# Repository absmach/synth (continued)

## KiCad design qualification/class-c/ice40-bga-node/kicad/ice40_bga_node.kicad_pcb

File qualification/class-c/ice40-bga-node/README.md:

# iCE40HX4K BGA node with a USB-C power input (Class C, case 1)

The board carries an iCE40HX4K FPGA in a 121-ball, 0.8 mm-pitch BGA with its supply chain, an SPI boot flash, one 12-pin header and four status LEDs. A USB-C receptacle powers it (power only) and a 6-pin header programs it. It has six copper layers and measures 59.9 x 43.5 mm.

It answers #328 under #40: a board with a BGA part, escaped under the pads, with via and fanout rules, made by an agent driving `synth mcp`. The board carries no firmware and has no USB data path. The figures below are measured on the board file or calculated from datasheets; nothing was built or measured on hardware.

The prompt to reproduce the board is in [`PROMPT.md`](PROMPT.md), written from the finished board. The prompts the agent ran are in the history at `0daaed69`.

## The board

### Parts

| Group                   | Parts                                                                                                                                     |
| ----------------------- | ----------------------------------------------------------------------------------------------------------------------------------------- |
| Power entry             | `J1` Korean Hroparts TYPE-C-31-M-12 USB-C receptacle (5 V from VBUS) with `R_CC1` and `R_CC2`, 5.1 k pull-downs on CC1 and CC2.           |
| Power entry             | `F1` Bourns MF-NSMF050-2 (0.5 A hold, 1 A trip, 13.2 V).                                                                                  |
| Power entry             | `D1` Nexperia PTVS6V0S1UR (6.0 V standoff, 6.67 V minimum breakdown, 10.3 V clamp at 38.8 A), and `C1`.                                   |
| Power entry             | No reverse-polarity stage, since a Type-C receptacle cannot be mated reversed.                                                            |
| CC protection           | `D8` and `D9` TPD1E10B06 bidirectional TVS diodes, one on each CC line at the receptacle, with no rail connection.                        |
| FPGA clock              | `X1`, 25 MHz oscillator on global buffer input `GBIN1` (`iot_197_gbin1`), decoupled by `C41`. The iCE40HX has no internal oscillator.     |
| 3.3 V                   | `U3` AMS1117-3.3 with 4 x 10 uF.                                                                                                          |
| 1.2 V core              | `U4` Texas Instruments TLV70012DDCR, TSOT-23-5, with 1 uF in and 1 uF + 4.7 uF out.                                                       |
| 1.2 V core              | PLL supply `VCCPLL` through the ferrite bead `FB1` (Murata BLM18AG601SN1D) and `C20` to `C22`.                                            |
| FPGA                    | `U1` Lattice iCE40HX4K-BG121 (`VPP_FAST` unconnected), every supply ball decoupled.                                                       |
| Configuration           | `U2` Winbond W25Q128JVSIQ, SOIC-8 208 mil (5.3 mm body), master SPI, with the 6-pin header `J2` for an external programmer.               |
| Configuration           | `CRESET_B` pulled up. `CDONE` drives its LED through N-FET `Q2`, so the open-drain `CDONE` net sees only a gate.                          |
| Programming header `J2` | Pins: `CFG_SS_B` (1, chip select), `CFG_SCK` (2), `CFG_SDI` (3), `CFG_SDO` (4), `CRESET_B` (5), ground (6).                               |
| Programming header `J2` | Names are from the FPGA's side: pin 3 is the flash output (MISO at the programmer) and pin 4 is the flash input (MOSI at the programmer). |
| Programming header `J2` | No 3.3 V pin. A programmer that senses target voltage needs a tap on `TP2`, which is on the 3.3 V rail.                                   |
| Programming procedure   | Hold `CRESET_B` low with an external programmer, write the flash `U2` over SPI, then release `CRESET_B` so the FPGA loads the bitstream.  |
| I/O                     | `J3` JXTCONN JXT-PZ2.54-1X12P-A1, 12 positions (3.3 V, ground and four FPGA I/O through 100 ohm series resistors).                        |
| Indicators              | Four LEDs in one row.                                                                                                                     |
| Test points             | `TP1` to `TP5` on 5 V, 3.3 V, 1.2 V, `CDONE` and `CRESET_B`, all on the bottom side of the board.                                                                              |
| Mounting                | Two M2.5 mounting holes at opposite corners (top left and bottom right), each 4.0 mm from its two board edges.                                                                  |
| FPGA `GNDPLL` | `gndpll0` and `gndpll1` are left unconnected. Lattice DS1040 v3.4, Signal Descriptions: the PLL ground connection is made on the FPGA, so `GNDPLL` must not be connected to the board ground. The PLL is not used. |

### Layout

| Item                    | Value                                                                                                                                                        |
| ----------------------- | ------------------------------------------------------------------------------------------------------------------------------------------------------------ |
| Outline                 | 59.9 x 45.7 mm                                                                                                                                               |
| Copper layers           | 6                                                                                                                                                            |
| Stackup                 | `manufacturer "jlc-advanced"` (the JLCPCB tier with the 0.2 mm drill and via-in-pad on six layers) and `requires via_in_pad`.                                |
| Parts in the BOM        | 63 lines: 56 parts with manufacturer, MPN, rating, datasheet and order number, and 7 board features with no part identity (2 mounting holes, 5 test points). |
| Parts placed in the CPL | 56                                                                                                                                                           |
| Nets                    | 31, all routed                                                                                                                                               |
| Track segments          | 357                                                                                                                                                          |
| Vias                    | 87: 19 at 0.35/0.2 mm, 19 at 0.46/0.2 mm, 49 at 0.6/0.3 mm.                                                                                                  |
| Track length            | 973.2 mm                                                                                                                                                    |
| Zones and planes        | `+3V3` is poured on the inner layers and ground on the outer layers. The 1.2 V core rail and the PLL supply are routed.                                      |
| USB-C placement         | `J1` sits on the left edge with its opening facing out (rotation 270). `escape { off }` is set on `J1`, which is not a ball grid.                            |
| BGA escape              | `escape { method underpad }` on `U1`. The 19 vias at 0.35/0.2 mm are filled and capped vias in the ball pads.                                                |
| Fab package             | `fab/gerbers.zip`, `fab/bom.csv`, `fab/cpl.csv`. `J2` and `J3` are hand-fit through-hole parts.                                                              |
| 3D models               | `models/` holds the STEP body of every part the board references and the board model `ice40_bga_node.step`. The board file reaches them by the relative path `${KIPRJMOD}/../models/`. Mounting holes and fiducials have no body. `J1` uses the HRO TYPE-C-31-M-12 STEP from github.com/ai03-2725/Type-C.pretty (the repository states no licence), placed to match KiCad's footprint. Any other part that KiCad's library has no model for is a simplified box of its envelope. |
| Schematic               | `images/schematic.pdf`: vector pages, one per sheet, plotted by `kicad-cli sch export pdf`. |

### Checks

| Check                              | Result                                             | Notes                                                                                                                                                                                                                                    |
| ---------------------------------- | -------------------------------------------------- | ---------------------------------------------------------------------------------------------------------------------------------------------------------------------------------------------------------------------------------------- |
| KiCad DRC (10.0.8, --refill-zones) | 0 errors, 0 unconnected, 3 warnings                | Warnings: 2 `silk_overlap`, 1 `silk_over_copper` (silkscreen cut back from vias and pads by the exporter, #425).                                                                                                                         |
| KiCad ERC (10.0.8)                 | 0 errors, 0 unconnected, 13 warnings               | Warnings: 8 `lib_symbol_issues`, 5 `lib_symbol_mismatch`.                                                                                                                                                                                |
| DRC rules file                     | Required for a clean DRC                           | `kicad/ice40_bga_node.kicad_dru` lowers the board floors (0.46 mm via diameter, 0.13 mm annular ring) to 0.35 mm and 0.075 mm for vias inside the courtyard of `U1` only.                                                                |
| DRC without the rules file         | `via_diameter` and `annular_width` errors          | Reported on the 19 via-in-pad vias. KiCad loads the rules file when it sits beside the board.                                                                                                                                            |
| Zone fill                          | Refilled                                           | The board is committed with refilled zones, and the Gerbers are plotted from that fill.                                                                                                                                                  |
| Dog-bone escape                    | Does not fit                                       | An export with `escape { method channel }` and without `requires via_in_pad` stopped at the plane stage: `net +3V3: no legal stitching-via position beside the pad at (38.00, 36.40) mm on Top`.                                         |
| Routing engine policy              | `engine_policy_verdict: rejected`                  | Under its strict-size policy, with no rule below the board floor.                                                                                                                                                                        |
| Routing engine via counts          | `claimed_total_vias: 30`, `claimed_via_in_pad: 33` | These count only the vias its own routing and fanout steps placed. Synth's later steps add plane, return and stitch vias and move vias out of pads that do not declare an under-pad escape. The Layout table gives the delivered values. |

### Design figures

| Area          | Item                                      | Value                                                                                                                                        | Basis                                                                     |
| ------------- | ----------------------------------------- | -------------------------------------------------------------------------------------------------------------------------------------------- | ------------------------------------------------------------------------- |
| Configuration | iCE40HX4K bitstream size                  | 135,183 bytes (1,081,464 bits)                                                                                                               | Lattice iCE40 Programming and Configuration, FPGA-TN-02001-3.4, Table 9.2 |
| Configuration | Flash capacity                            | 128 Mbit, holds the bitstream                                                                                                                | Winbond W25Q128JV datasheet                                               |
| Thermal       | `U3` dissipation formula                  | `(5.0 - 3.3) x I`                                                                                                                            | calculated                                                                |
| Thermal       | AMS1117 junction limit                    | 125 degC                                                                                                                                     | AMS1117 datasheet                                                         |
| Thermal       | AMS1117 SOT-223 theta-JA                  | 46 to more than 90 degC/W, depending on copper area; the budget uses 90 degC/W                                                               | AMS1117 datasheet                                                         |
| Power         | `+3V3` load: `U4` TLV70012                | 200 mA (rated output; a linear regulator draws it from the input)                                                                            | TI TLV700 datasheet SBVS173, recommended operating conditions             |
| Power         | `+3V3` load: `U2` W25Q128JV               | 25 mA (`ICC5` and `ICC7` maximum, program and erase)                                                                                         | Winbond W25Q128JV datasheet, DC electrical characteristics                |
| Power         | `+3V3` load: four LEDs with 1 k resistors | 1.3 mA                                                                                                                                       | calculated in the source                                                  |
| Power         | `+3V3` total load                         | 226 mA. The loads are datasheet maxima added together; no operating state reaches all of them at once.                                       | calculated                                                                |
| Thermal       | `U3` at 226 mA                            | 0.38 W, a 35 degC rise: Tj 60 degC at 25 degC ambient, 105 degC at 70 degC ambient                                                           | calculated                                                                |
| Thermal       | Headroom for `J3`                         | About 0.43 A more at 25 degC ambient, or 0.13 A at 70 degC, before Tj reaches 125 degC                                                       | calculated                                                                |
| Thermal       | `F1` bound                                | 0.5 A hold bounds `U3` dissipation at 0.85 W (Tj 101 degC at 25 degC ambient)                                                                | calculated                                                                |
| Thermal       | Warning `W-SYNTH-THERMAL-001`             | Comes from the registry part's 1200 mW package rating at 90 degC/W, not from this board's load                                               | Synth registry part                                                       |
| Protection    | `VBUS`                                    | `D1` (6.0 V standoff) protects `VBUS`.                                                                                                       | Nexperia PTVS6V0S1UR datasheet                                            |
| Protection    | CC lines                                  | `D8` and `D9` (5.5 V standoff) have no connection to `VBUS`, so a source that drives CC before VBUS cannot back-power the rail through them. | TI TPD1E10B06 datasheet                                                   |
| Protection    | `J3`                                      | Carries FPGA I/O through 100 ohm series resistors and has no protection device.                                                              | measured on the board file                                                |
| Assembly      | Via-in-pad land                           | JLCPCB's via-in-pad guide gives the land as the drill plus 0.15 mm.                                                                          | JLCPCB via-in-pad guide                                                   |

### Sourcing

| Item                      | Status                    | Notes                                                                                                                                       |
| ------------------------- | ------------------------- | ------------------------------------------------------------------------------------------------------------------------------------------- |
| `U2` W25Q128JVSIQ package | Checked                   | Manufacturer listings (LCSC, Arrow, RS, JITX) give an 8-pin SOIC of 208 mil. The footprint is `Package_SO:SOIC-8_5.3x5.3mm_P1.27mm`.        |
| `U4` TLV70012 package     | Checked                   | Listed at LCSC only in the DDC (thin) package, which the footprint `TSOT-23-5` matches. Pinout same as DBV: 1 IN, 2 GND, 3 EN, 4 NC, 5 OUT. |
| `D8`, `D9`                | Ordered as TPD1E10B06DYAR | SOD-523, LCSC C3712135, not the DPY X1SON package.                                                                                          |
| `U1` stock                | Unclear                   | The LCSC page for `U1` does not show clear stock. DigiKey 220-2147-ND is the alternative.                                                   |
| LCSC stock figures        | Not firm                  | Stock figures changed between page reads in 2026-11.                                                                                        |

## Not verified by Synth

| Area                 | What is not verified                                                                       |
| -------------------- | ------------------------------------------------------------------------------------------ |
| USB data             | The board has no USB data path. `J1` is a power-only USB-C input.                          |
| Return paths         | The return-path rule is applied by the export gate, and no per-via check is recorded here. |
| CC attach            | No attach test on a 3 A charger was run with the CC diodes `D8` and `D9` fitted.           |
| ESD level            | The board is a bench programming node. No IEC 61000-4-2 level is claimed.                  |
| Thermal              | The 3.3 V budget is calculated from datasheet figures. No temperature was measured.        |
| DFM                  | No JLCDFM or BOM-matching run is recorded.                                                 |
| Independent sign-off | The independent PCB review required by #40 is still open.                                  |

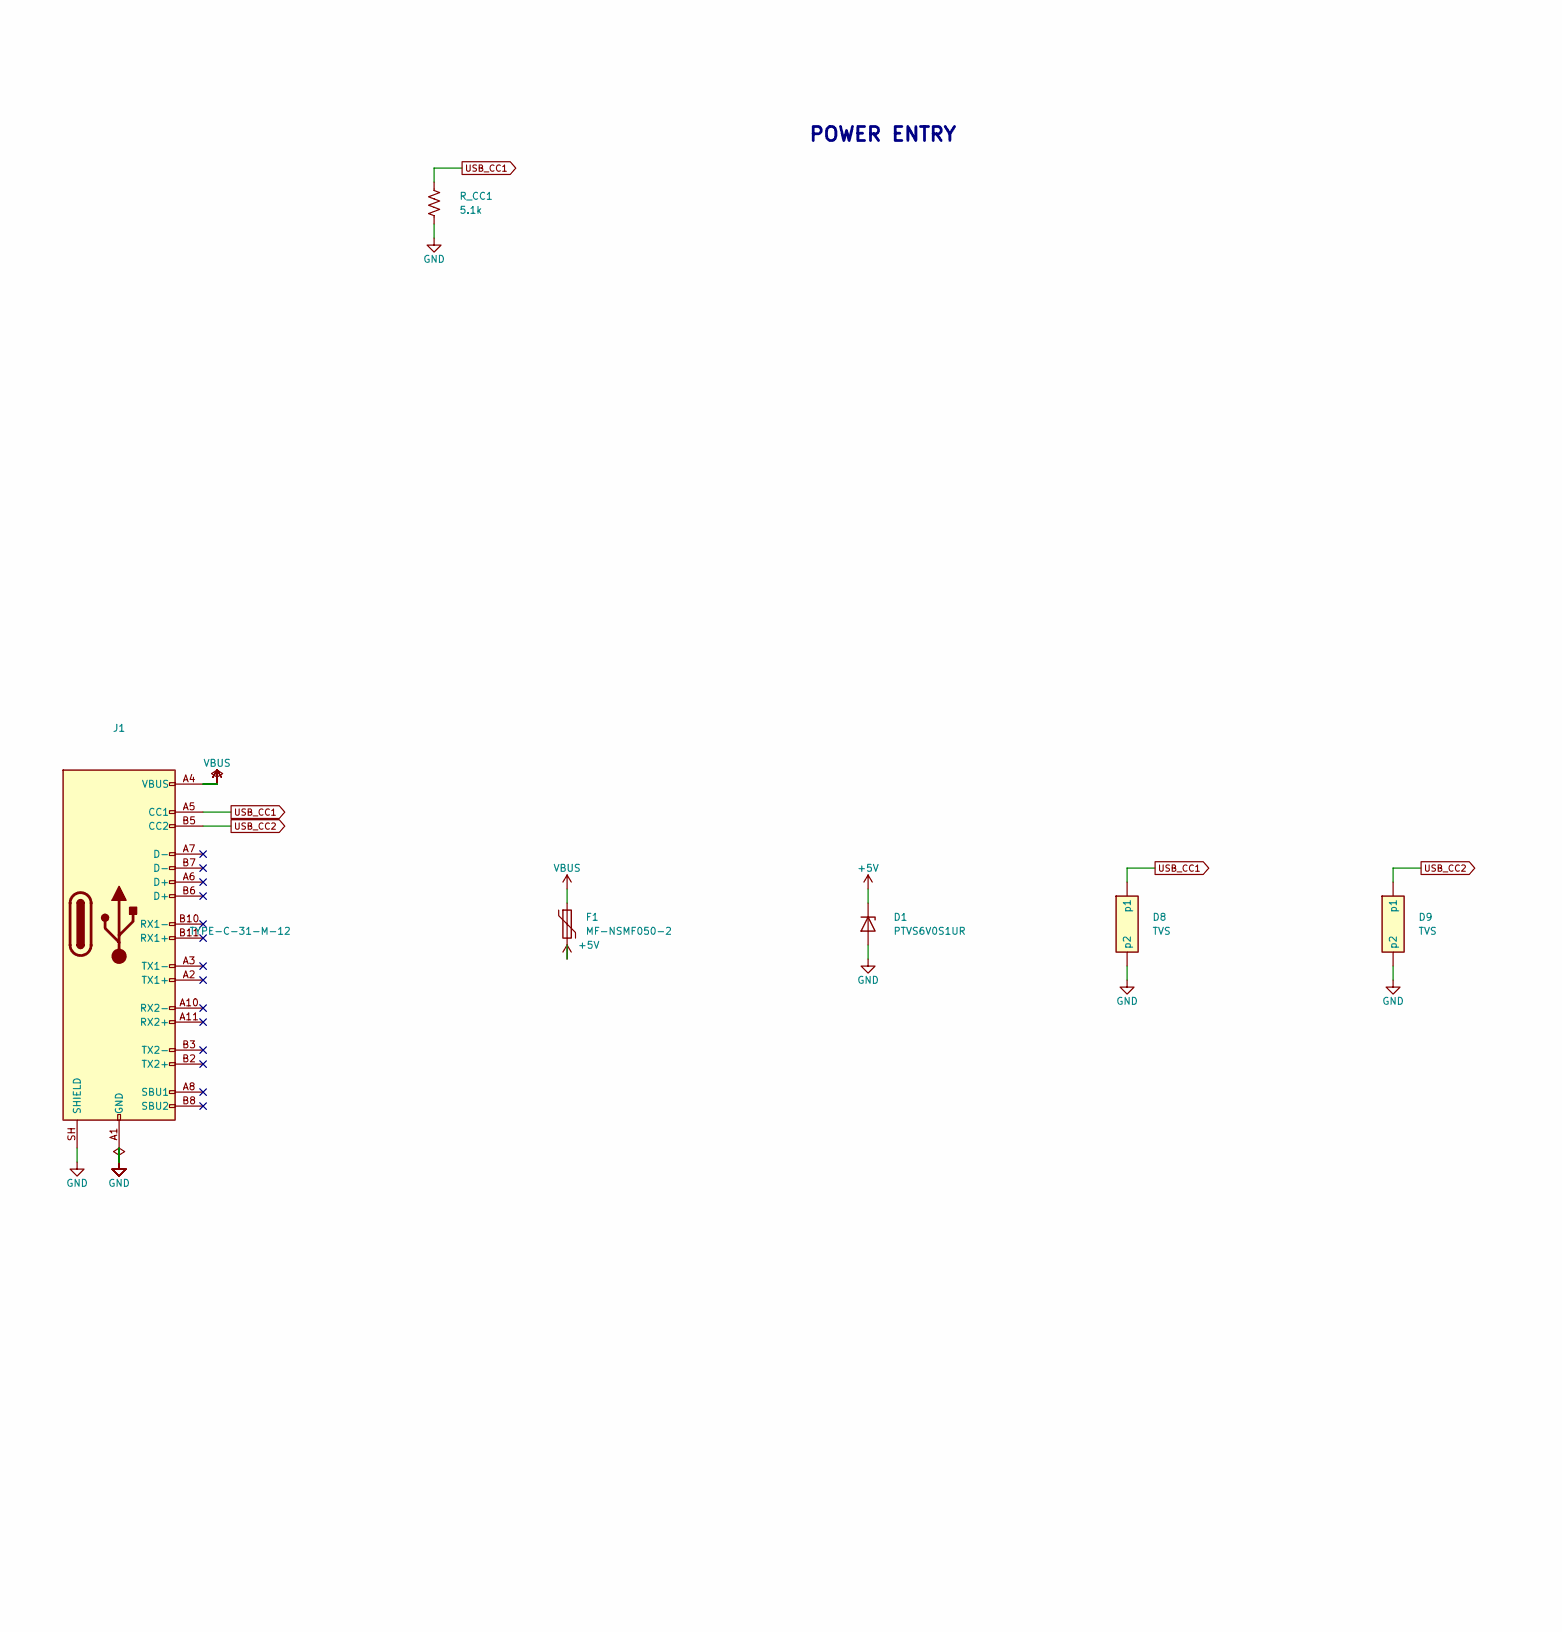
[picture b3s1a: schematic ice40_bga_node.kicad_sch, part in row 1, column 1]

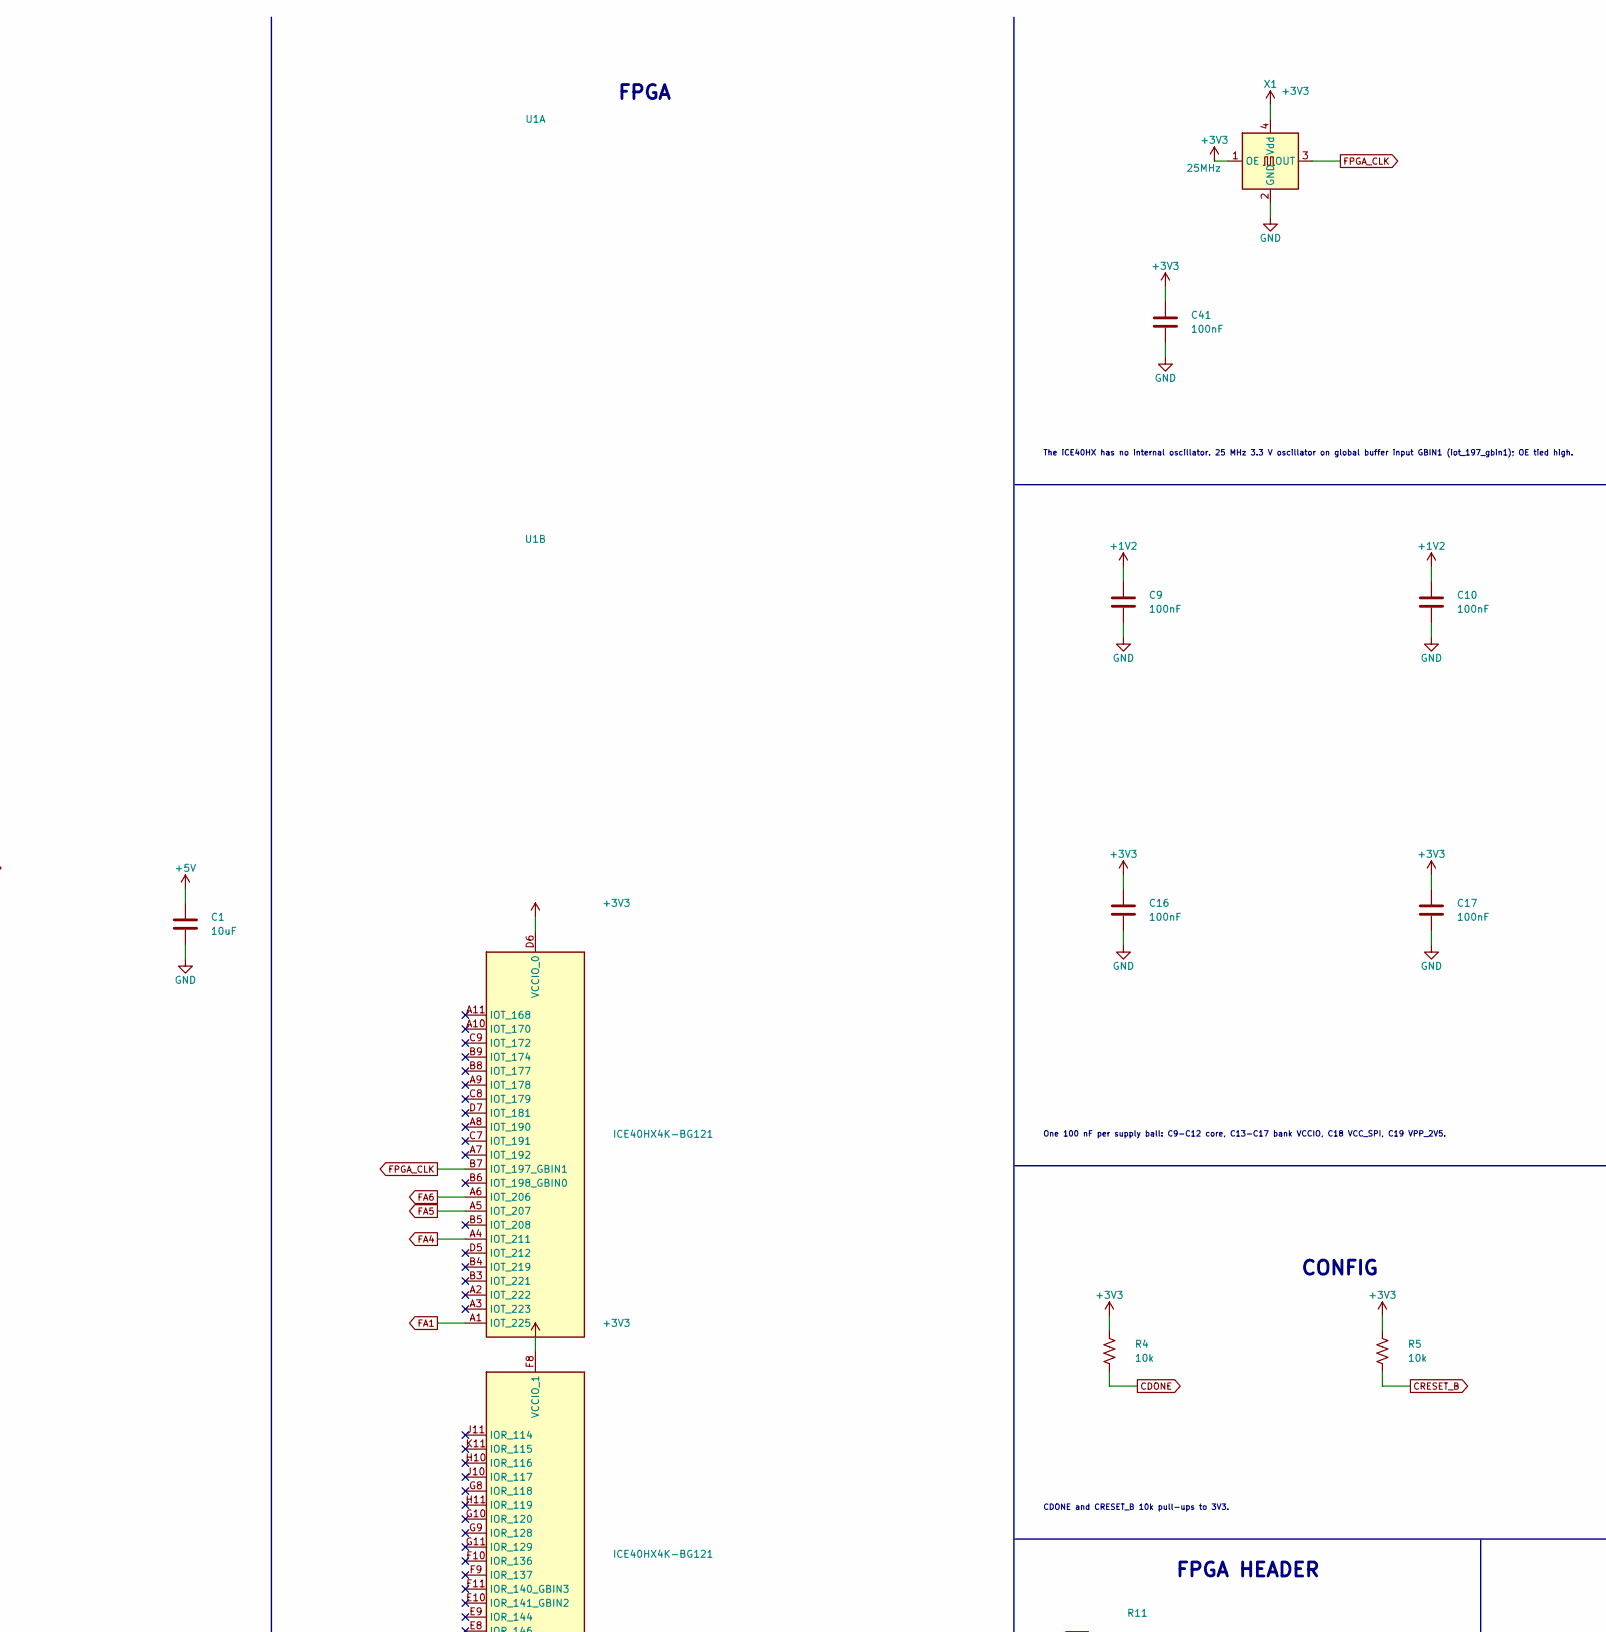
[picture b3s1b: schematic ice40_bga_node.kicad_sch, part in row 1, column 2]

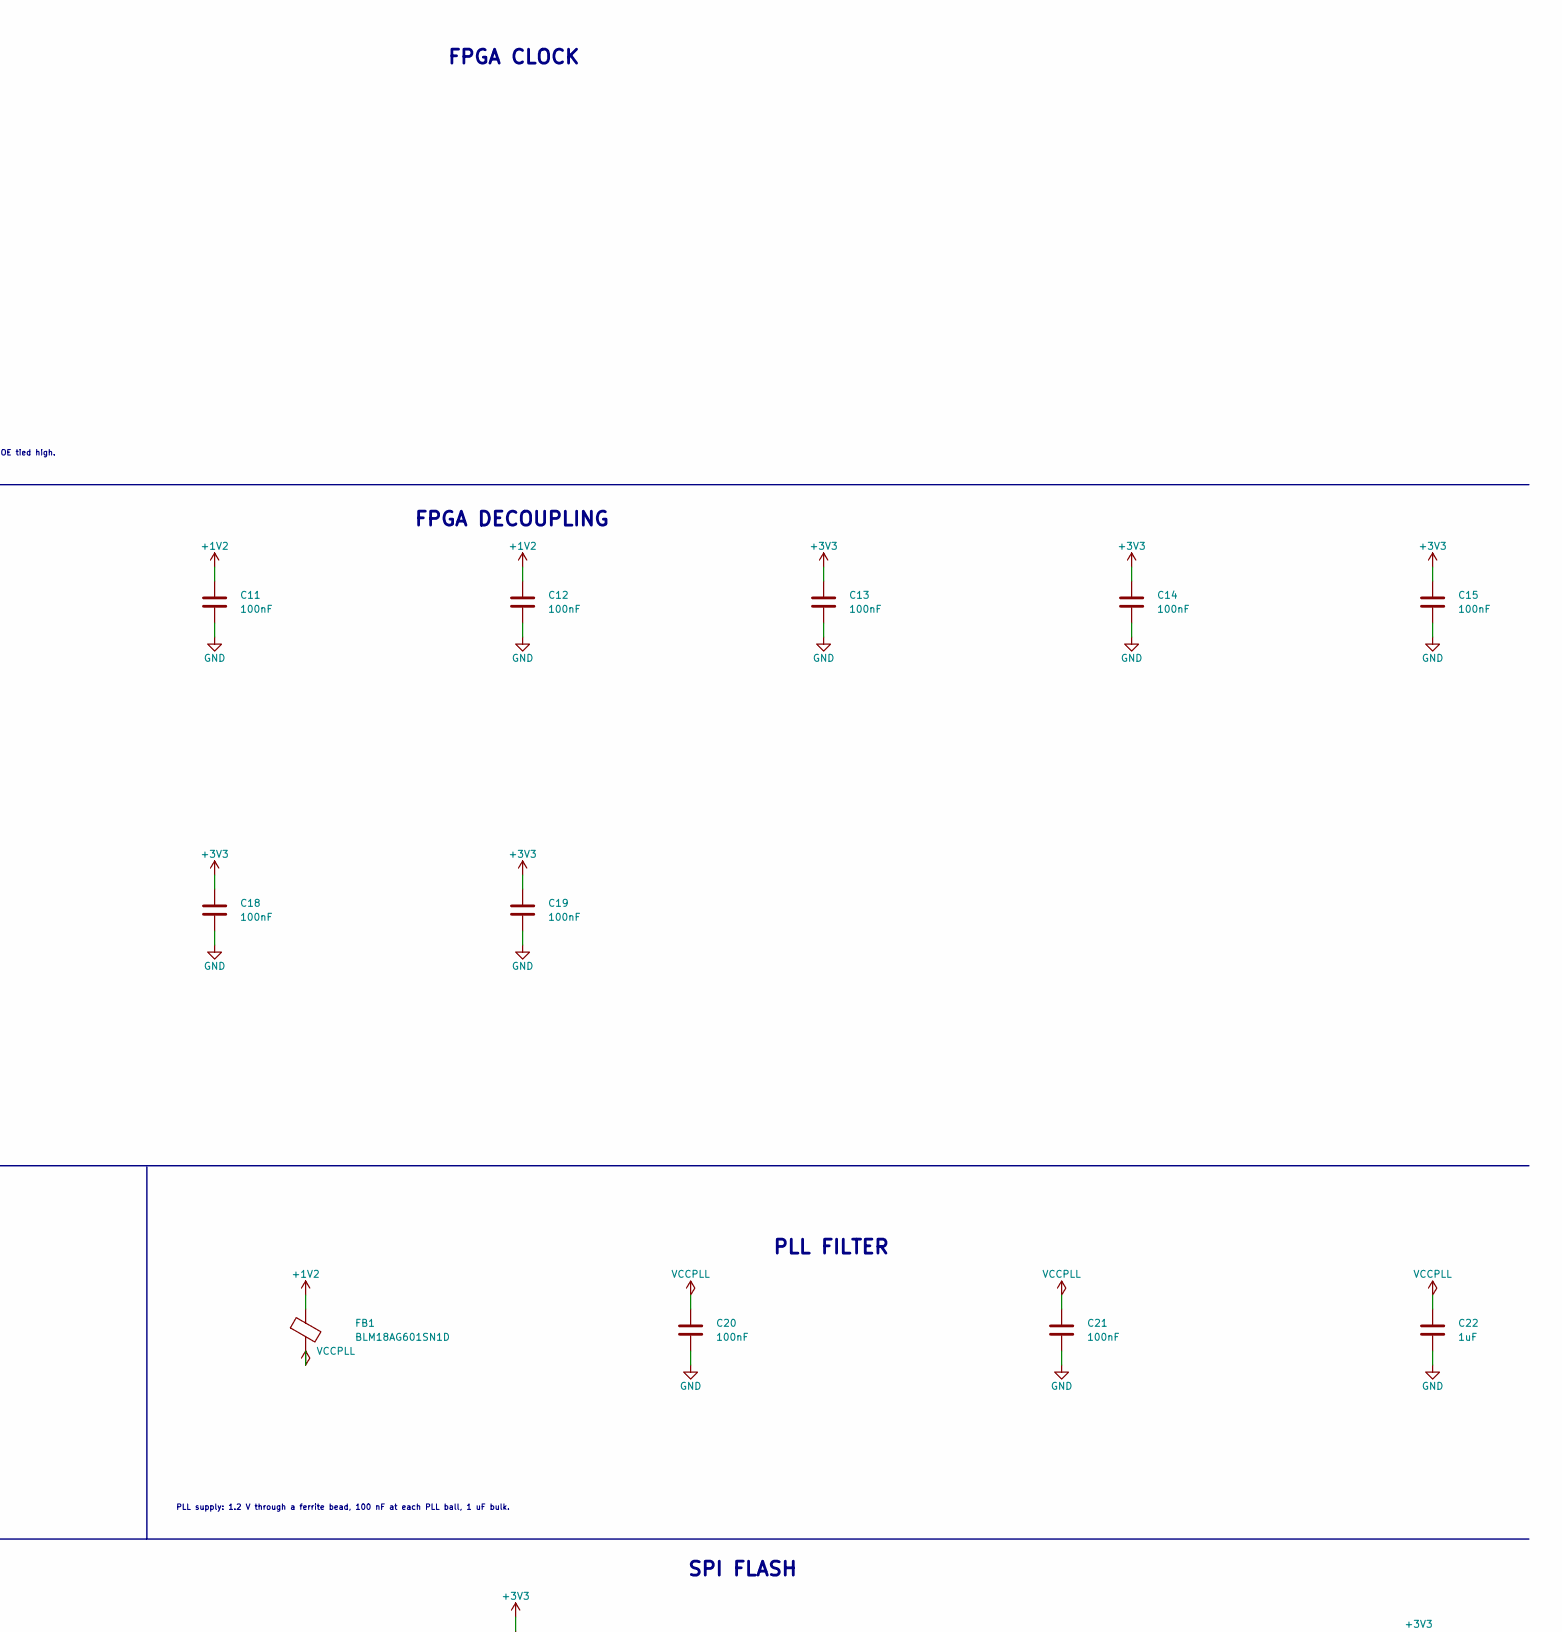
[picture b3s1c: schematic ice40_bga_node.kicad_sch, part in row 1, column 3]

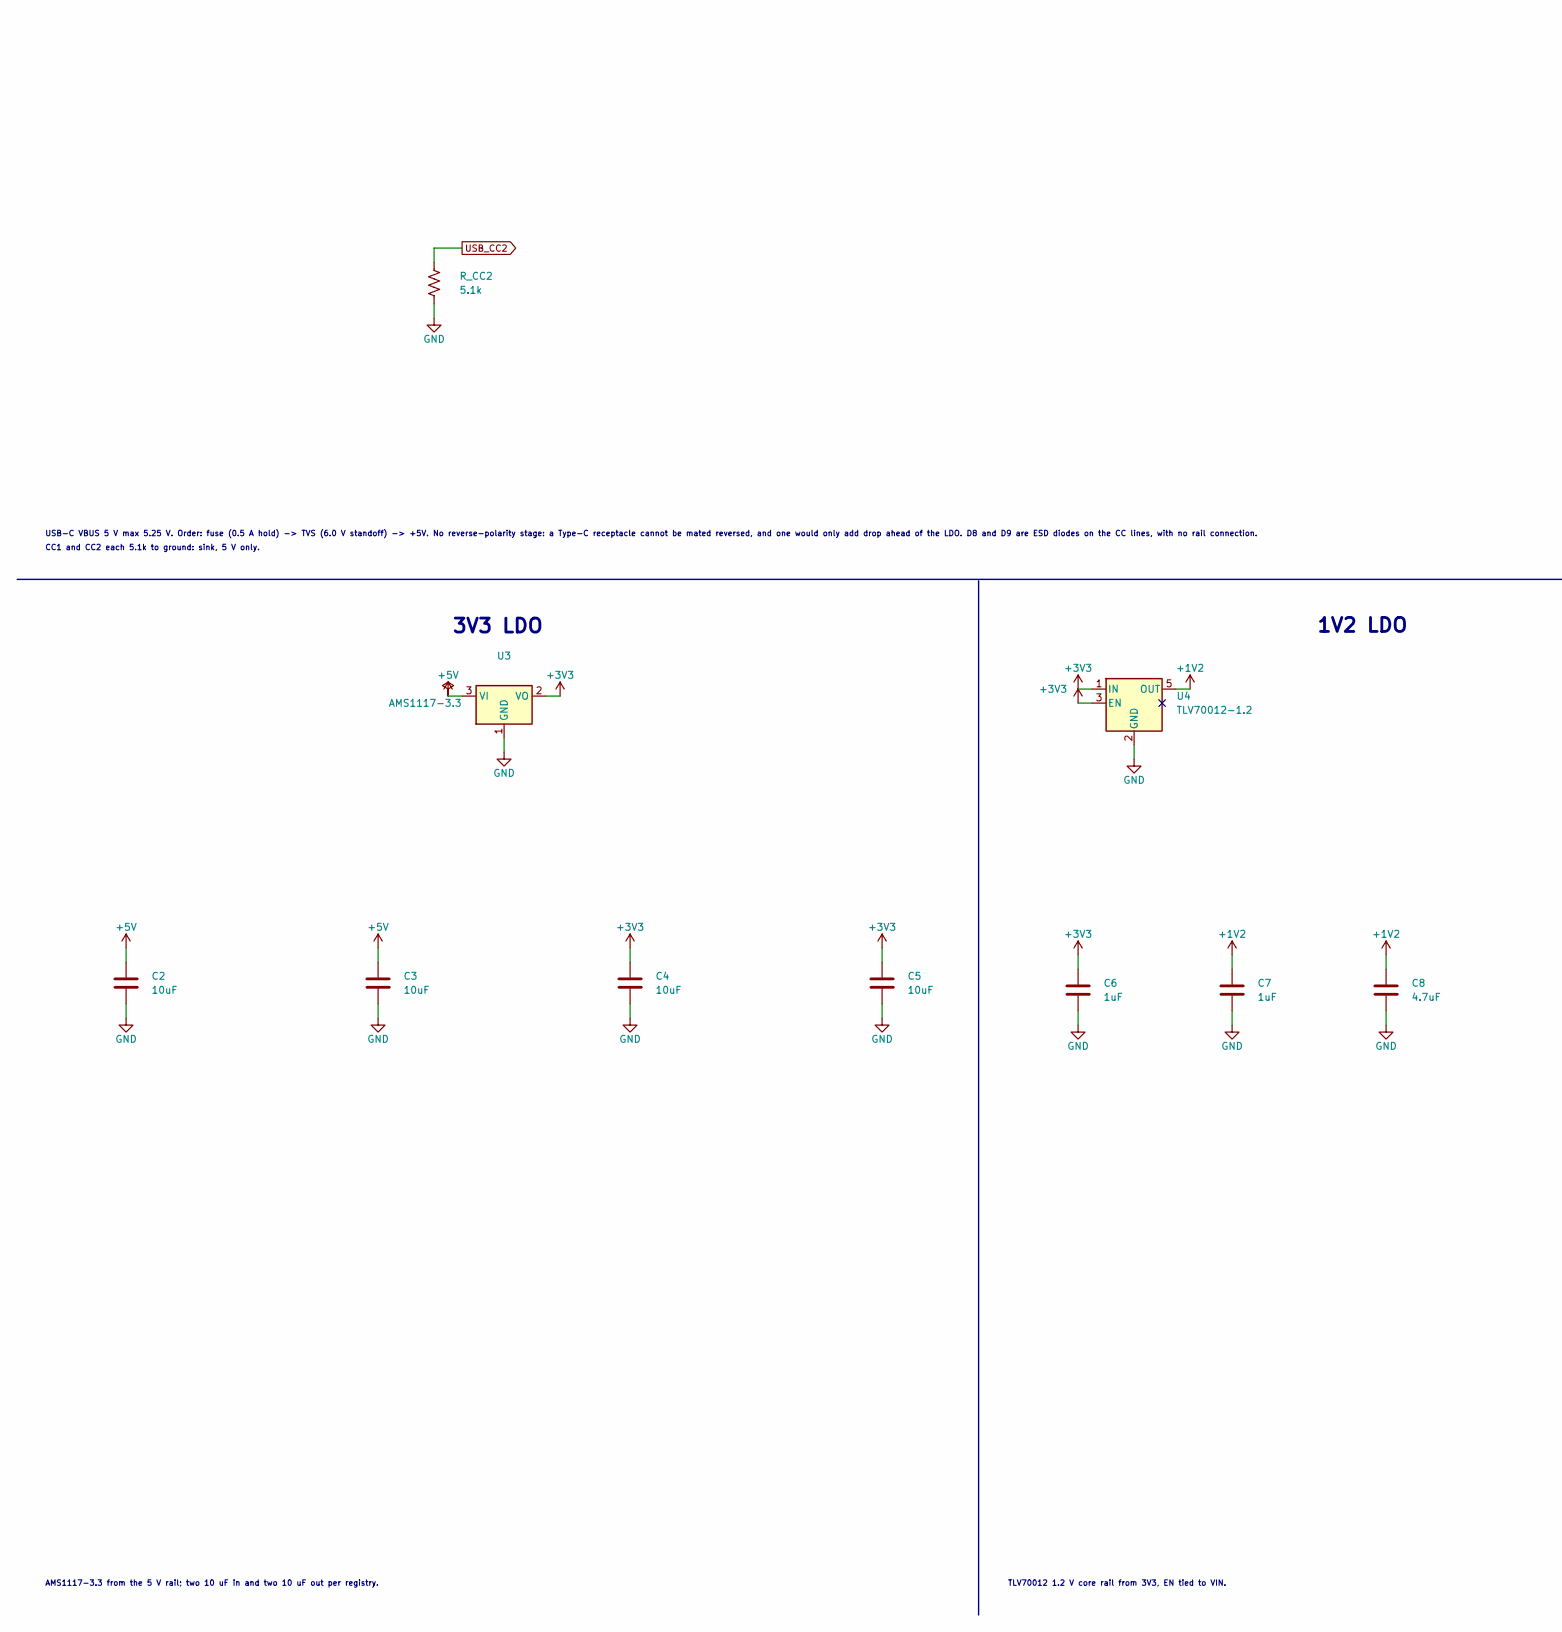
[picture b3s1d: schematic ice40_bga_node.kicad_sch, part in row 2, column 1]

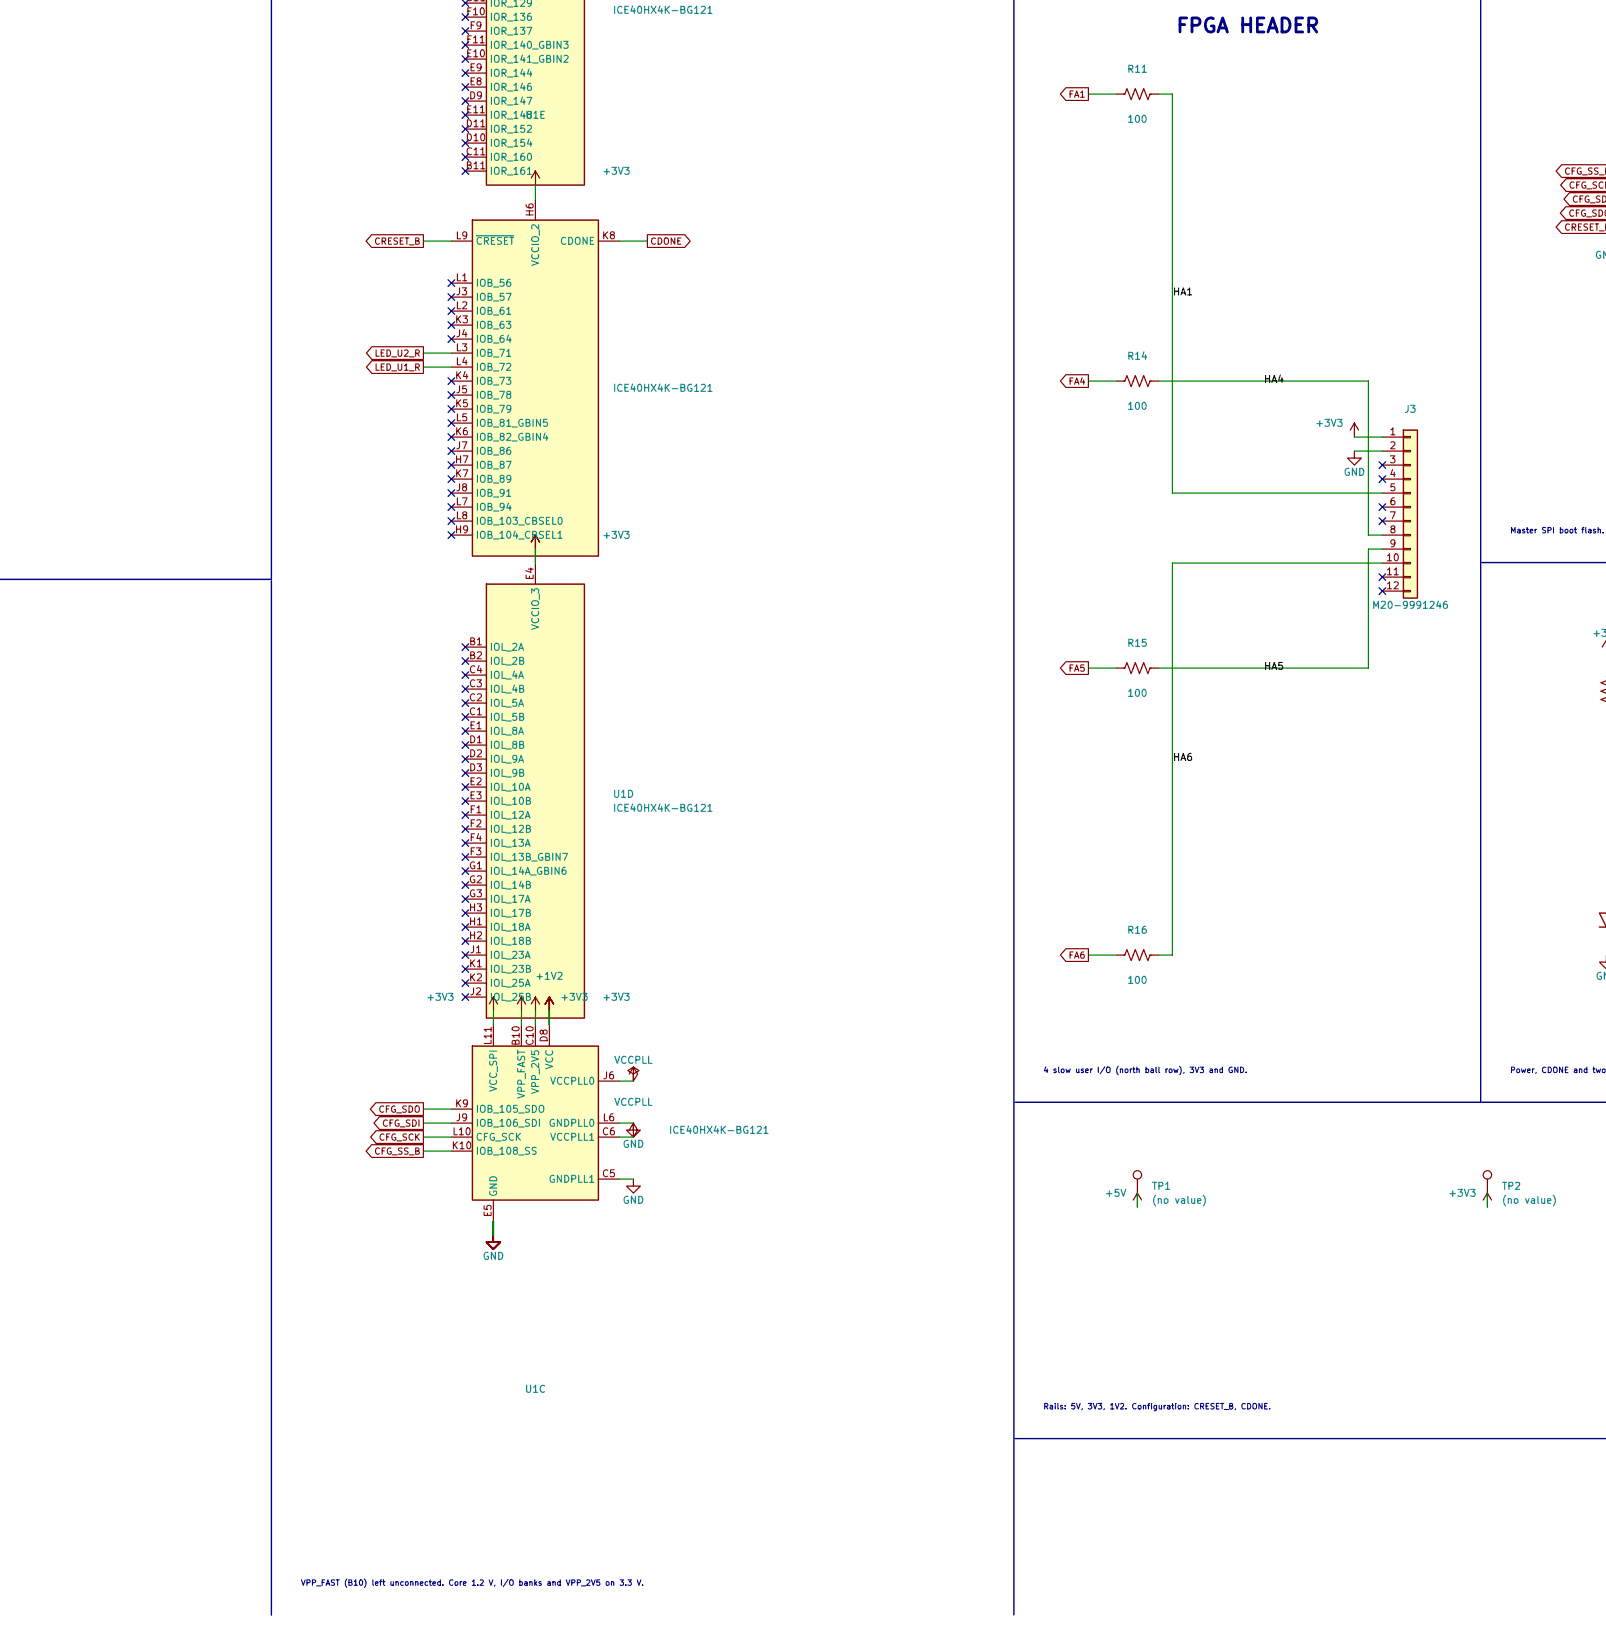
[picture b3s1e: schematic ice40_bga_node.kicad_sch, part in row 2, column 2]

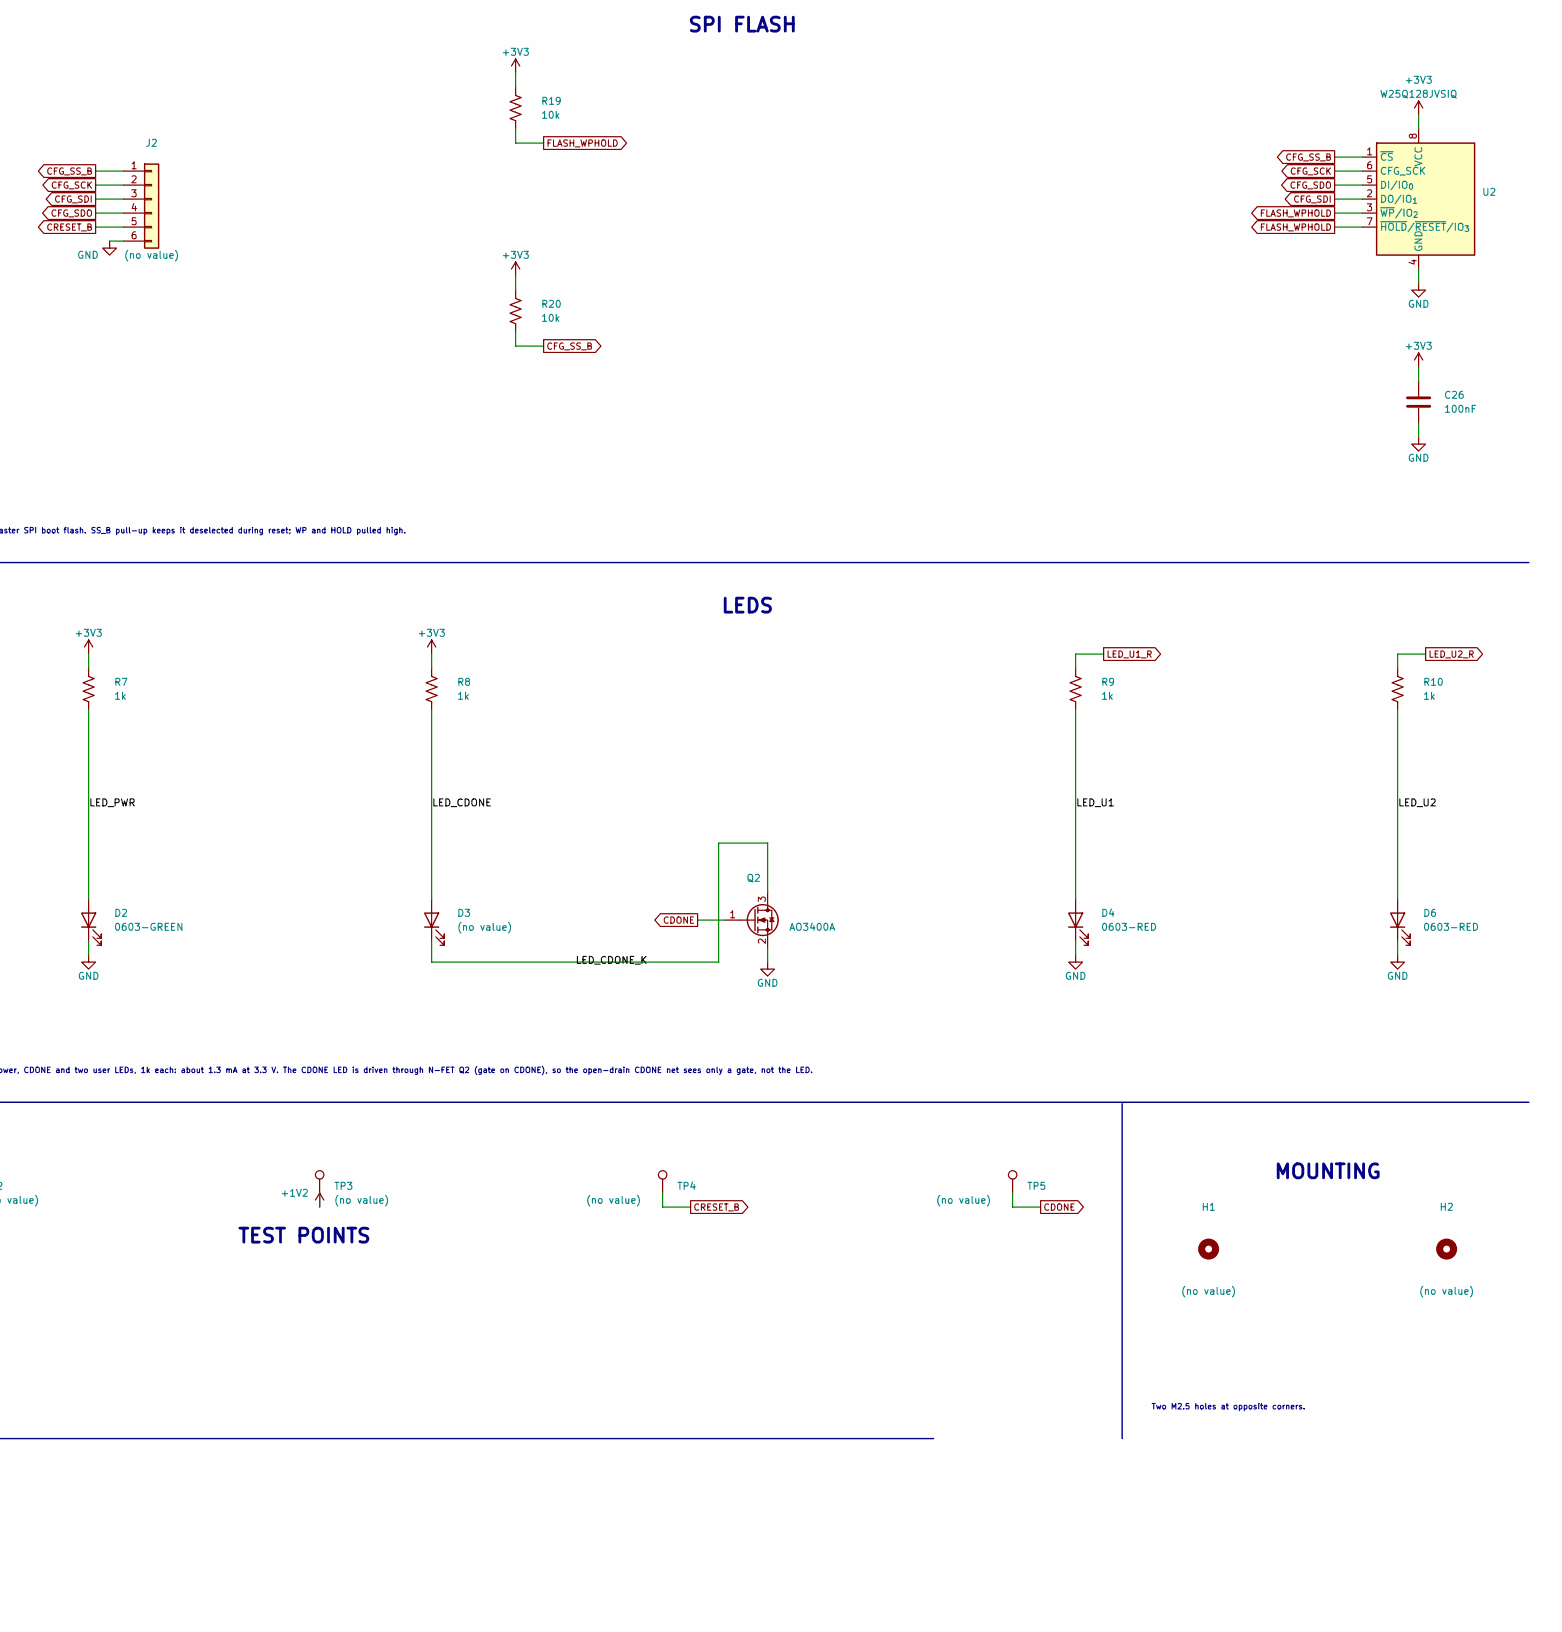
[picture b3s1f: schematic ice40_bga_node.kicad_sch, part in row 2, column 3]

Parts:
C1, C2, C3, C4, C5: 10uF; C_0805_2012Metric
C6, C7, C22: 1uF; C_0603_1608Metric
C8: 4.7uF; C_0805_2012Metric
C9, C10, C11, C12, C13, C14, C15, C16, C17, C18, C19, C20, C21, C26, C41: 100nF; C_0402_1005Metric
D1: PTVS6V0S1UR; Nexperia_CFP3_SOD-123W; MPN PTVS6V0S1UR
D2: 0603-GREEN; LED_0603_1608Metric; MPN 0603-GREEN; LCSC C72043
D3: (no value); LED_0603_1608Metric
D4, D6: 0603-RED; LED_0603_1608Metric; MPN 0603-RED; LCSC C2286
D8, D9: TVS; D_SOD-523; MPN TPD1E10B06DYAR
F1: MF-NSMF050-2; Fuse_1206_3216Metric; MPN MF-NSMF050-2; LCSC C75464
FB1: BLM18AG601SN1D; L_0603_1608Metric; MPN BLM18AG601SN1D; LCSC C19330
H1, H2: (no value); MountingHole_2.5mm
J1: TYPE-C-31-M-12; USB_C_Receptacle_HRO_TYPE-C-31-M-12; MPN TYPE-C-31-M-12; LCSC C165948
J2: (no value); PinHeader_1x06_P2.54mm_Vertical
J3: M20-9991246; PinHeader_1x12_P2.54mm_Vertical; MPN M20-9991246
Q2: AO3400A; SOT-23; MPN AO3400A
R4, R5, R19, R20: 10k; R_0402_1005Metric
R7, R8, R9, R10: 1k; R_0603_1608Metric
R11, R14, R15, R16: 100; R_0402_1005Metric
R_CC1, R_CC2: 5.1k; R_0402_1005Metric
TP1, TP2, TP3, TP4, TP5: (no value); TestPoint_Pad_D1.5mm
U1: ICE40HX4K-BG121; BGA-121_9.0x9.0mm_Layout11x11_P0.8mm_Ball0.4mm_Pad0.35mm_NS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; MPN ICE40HX4K-BG121
U2: W25Q128JVSIQ; SOIC-8_5.3x5.3mm_P1.27mm; MPN W25Q128JVSIQ; LCSC C97521
U3: AMS1117-3.3; SOT-223-3_TabPin2; MPN AMS1117-3.3; LCSC C6186
U4: TLV70012-1.2; TSOT-23-5; MPN TLV70012DDCR; LCSC C69446
X1: 25MHz; Oscillator_SMD_SiT_PQFN-4Pin_5.0x3.2mm

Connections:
+1V2: C7.1, C8.1, C9.1, C10.1, C11.1, C12.1, FB1.1, TP3.1, U1.D4 (VCC), U1.D8 (VCC), U1.H4 (VCC), U1.H8 (VCC), U4.5 (OUT)
+3V3: C4.1, C5.1, C6.1, C13.1, C14.1, C15.1, C16.1, C17.1, C18.1, C19.1, C26.1, C41.1, J3.1, R4.1, R5.2, R7.1, R8.1, R19.1, R20.1, TP2.1, U1.B10 (VPP_FAST), U1.C10 (VPP_2V5), U1.D6 (VCCIO_0), U1.E4 (VCCIO_3), U1.F8 (VCCIO_1), U1.G4 (VCCIO_3), U1.H6 (VCCIO_2), U1.L11 (VCC_SPI), U2.8 (VCC), U3.2 (VO), U4.1 (IN), U4.3 (EN), X1.1 (OE), X1.4 (Vdd)
+5V: C1.1, C2.1, C3.1, D1.1 (K), F1.2, TP1.1, U3.3 (VI)
CDONE: Q2.1 (G), R4.2, TP5.1, U1.K8 (CDONE)
CFG_SCK: J2.2, U1.L10 (IOB_107_SCK), U2.6 (CLK)
CFG_SDI: J2.3, U1.J9 (IOB_106_SDI), U2.2 (DO/IO_{1})
CFG_SDO: J2.4, U1.K9 (IOB_105_SDO), U2.5 (DI/IO_{0})
CFG_SS_B: J2.1, R20.2, U1.K10 (IOB_108_SS), U2.1 (~CS)
CRESET_B: J2.5, R5.1, TP4.1, U1.L9 (~CRESET)
FA1: R11.1, U1.A1 (IOT_225), U1.B1 (IOL_2A)
FA4: R14.1, U1.A4 (IOT_211), U1.A9 (IOT_178), U1.B4 (IOT_219), U1.B9 (IOT_174)
FA5: R15.1, U1.A5 (IOT_207)
FA6: R16.1, U1.A6 (IOT_206), U1.B6 (IOT_198_GBIN0)
FLASH_WPHOLD: R19.2, U2.3 (~WP/IO_{2}), U2.7 (~HOLD/~RESET/IO_{3})
FPGA_CLK: U1.A7 (IOT_192), U1.B7 (IOT_197_GBIN1), X1.3 (OUT)
GND: C1.2, C2.2, C3.2, C4.2, C5.2, C6.2, C7.2, C8.2, C9.2, C10.2, C11.2, C12.2, C13.2, C14.2, C15.2, C16.2, C17.2, C18.2, C19.2, C20.2, C21.2, C22.2, C26.2, C41.2, D1.2 (A), D2.1 (K), D4.1 (K), D6.1 (K), D8.2 (p2), D9.2 (p2), J1.A1 (GND), J1.A12 (GND), J1.B1 (GND), J1.B12 (GND), J1.SH (SHIELD), J2.6, J3.2, Q2.2 (S), R_CC1.2, R_CC2.2, U1.C5 (GNDPLL1), U1.E5 (GND), U1.E6 (GND), U1.E7 (GND), U1.F5 (GND), U1.F6 (GND), U1.F7 (GND), U1.G5 (GND), U1.G6 (GND), U1.G7 (GND), U1.H5 (GND), U1.L6 (GNDPLL0), U2.4 (GND), U3.1 (GND), U4.2 (GND), X1.2 (GND)
HA1: J3.5, R11.2
HA4: J3.8, R14.2
HA5: J3.9, R15.2
HA6: J3.10, R16.2
LED_CDONE: D3.2 (A), R8.2
LED_CDONE_K: D3.1 (K), Q2.3 (D)
LED_PWR: D2.2 (A), R7.2
LED_U1: D4.2 (A), R9.2
LED_U1_R: R9.1, U1.L4 (IOB_72)
LED_U2: D6.2 (A), R10.2
LED_U2_R: R10.1, U1.L3 (IOB_71)
USB_CC1: D8.1 (p1), J1.A5 (CC1), R_CC1.1
USB_CC2: D9.1 (p1), J1.B5 (CC2), R_CC2.1
VBUS: F1.1, J1.A4 (VBUS), J1.A9 (VBUS), J1.B4 (VBUS), J1.B9 (VBUS)
VCCPLL: C20.1, C21.1, C22.1, FB1.2, U1.C6 (VCCPLL1), U1.J6 (VCCPLL0)

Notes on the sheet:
POWER ENTRY
3V3 LDO
1V2 LDO
FPGA
FPGA CLOCK
FPGA DECOUPLING
PLL FILTER
CONFIG
SPI FLASH
LEDS
FPGA HEADER
TEST POINTS
MOUNTING
USB-C VBUS 5 V max 5.25 V. Order: fuse (0.5 A hold) -> TVS (6.0 V standoff) -> +5V. No reverse-polarity stage: a Type-C receptacle cannot be mated reversed, and one would only add drop ahead of the LDO. D8 and D9 are ESD diodes on the CC lines, with no rail connection.
CC1 and CC2 each 5.1k to ground: sink, 5 V only.
AMS1117-3.3 from the 5 V rail; two 10 uF in and two 10 uF out per registry.
TLV70012 1.2 V core rail from 3V3, EN tied to VIN.
VPP_FAST (B10) left unconnected. Core 1.2 V, I/O banks and VPP_2V5 on 3.3 V.
The iCE40HX has no internal oscillator. 25 MHz 3.3 V oscillator on global buffer input GBIN1 (iot_197_gbin1); OE tied high.
One 100 nF per supply ball: C9-C12 core, C13-C17 bank VCCIO, C18 VCC_SPI, C19 VPP_2V5.
PLL supply: 1.2 V through a ferrite bead, 100 nF at each PLL ball, 1 uF bulk.
CDONE and CRESET_B 10k pull-ups to 3V3.
Master SPI boot flash. SS_B pull-up keeps it deselected during reset; WP and HOLD pulled high.
Power, CDONE and two user LEDs, 1k each: about 1.3 mA at 3.3 V. The CDONE LED is driven through N-FET Q2 (gate on CDONE), so the open-drain CDONE net sees only a gate, not the LED.
4 slow user I/O (north ball row), 3V3 and GND.
Rails: 5V, 3V3, 1V2. Configuration: CRESET_B, CDONE.
Two M2.5 holes at opposite corners.
